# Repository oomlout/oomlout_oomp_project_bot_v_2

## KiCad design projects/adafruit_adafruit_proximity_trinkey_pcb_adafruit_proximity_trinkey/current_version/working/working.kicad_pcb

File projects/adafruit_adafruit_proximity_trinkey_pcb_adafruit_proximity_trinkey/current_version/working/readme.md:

# adafruit_proximity_trinkey_pcb
 
## summary 
* id: adafruit_adafruit_proximity_trinkey_pcb_adafruit_proximity_trinkey
* user: adafruit
* name: adafruit_proximity_trinkey_pcb
* board: adafruit_proximity_trinkey
* repo: https://github.com/adafruit/Adafruit-Proximity-Trinkey-PCB

* src_file_repo_sch: 
* src_file_repo_sch_link: https://github.com/adafruit/Adafruit-Proximity-Trinkey-PCB/tree/main/
* full details link: https://github.com/oomlout/oomlout_oomp_project_bot_v_2/tree/main/projects/adafruit_adafruit_proximity_trinkey_pcb_adafruit_proximity_trinkey/current_version/working  

## schematic  
  
[schematic (pdf)](working_schematic.pdf) 

## pcb  

[board (pdf)](working.pdf)  

## working_bom
| Id | Designator | Footprint | Quantity | Designation | Supplier and ref |  | None | 
| --- | --- | --- | --- | --- | --- | --- | --- | 
| 1 | R1,R2 | 0603-NO | 2 | 4.7K |  |  | [''] | 
| 2 | FID1,FID2 | FIDUCIAL_1MM | 2 | FIDUCIAL_1MM |  |  | [''] | 
| 3 | C3,C8 | 0805-NO | 2 | 10uF |  |  | [''] | 
| 4 | C4,C5 | 0603-NO | 2 | 1uF |  |  | [''] | 
| 5 | IC3 | QFN32_5MM | 1 | ATSAMD21E |  |  | [''] | 
| 6 | LED1,LED2 | LED3535 | 2 | WS2812B3535 |  |  | [''] | 
| 7 | U3 | APDS-9960 | 1 | APDS-9960 |  |  | [''] | 
| 8 | U1 | SOT23-5 | 1 | AP2112K-3.3 |  |  | [''] | 
| 9 | CN1 | USBA_PCB | 1 | USB A |  |  | [''] | 
| 10 | Q2 | BTN_KMR2_4.6X2.8 | 1 | reset |  |  | [''] | 
| 11 | SWD0,RST0 | TP16R | 2 | TPTP16R |  |  | [''] | 
| 12 | TP1,TP2 | TESTPOINT_ROUND_1.5MM_NO | 2 |  |  |  | [''] | 
| 13 | SWC0 | TP15R | 1 | TPTP15R |  |  | [''] | 
| 14 | U$8 | PCBFEAT-REV-040 | 1 |  |  |  | [''] | 
| 15 | U$10 | ADAFRUIT_9MM | 1 |  |  |  | [''] | 

## bom_schematic
| Ref | Qnty | Value | Cmp name | Footprint | Description | Vendor | DNP | 
| --- | --- | --- | --- | --- | --- | --- | --- | 
| C3, C8 | 2 | 10uF | CAP_CERAMIC0805-NOOUTLINE | working:0805-NO |  |  |  | 
| C4, C5 | 2 | 1uF | CAP_CERAMIC0603_NO | working:0603-NO |  |  |  | 
| CN1 | 1 | USB A | USB_TYPEAPCB | working:USBA_PCB |  |  |  | 
| FID1, FID2 | 2 | FIDUCIAL_1MM | FIDUCIAL_1MM | working:FIDUCIAL_1MM |  |  |  | 
| IC3 | 1 | ATSAMD21E | ATSAMD21E | working:QFN32_5MM |  |  |  | 
| LED1, LED2 | 2 | WS2812B3535 | WS2812B3535 | working:LED3535 |  |  |  | 
| Q2 | 1 | reset | SWITCH_TACT_SMT4.6X2.8 | working:BTN_KMR2_4.6X2.8 |  |  |  | 
| R1, R2 | 2 | 4.7K | RESISTOR_0603_NOOUT | working:0603-NO |  |  |  | 
| RST0 | 1 | TPTP16R | TPTP16R | working:TP16R |  |  |  | 
| SWC0 | 1 | TPTP15R | TPTP15R | working:TP15R |  |  |  | 
| SWD0 | 1 | TPTP16R | TPTP16R | working:TP16R |  |  |  | 
| TP1, TP2 | 2 | TESTPOINTROUND1.5MMNO | TESTPOINTROUND1.5MMNO | working:TESTPOINT_ROUND_1.5MM_NO |  |  |  | 
| U1 | 1 | AP2112K-3.3 | VREG_SOT23-5 | working:SOT23-5 |  |  |  | 
| U3 | 1 | APDS-9960 | APDS-9960 | working:APDS-9960 |  |  |  |

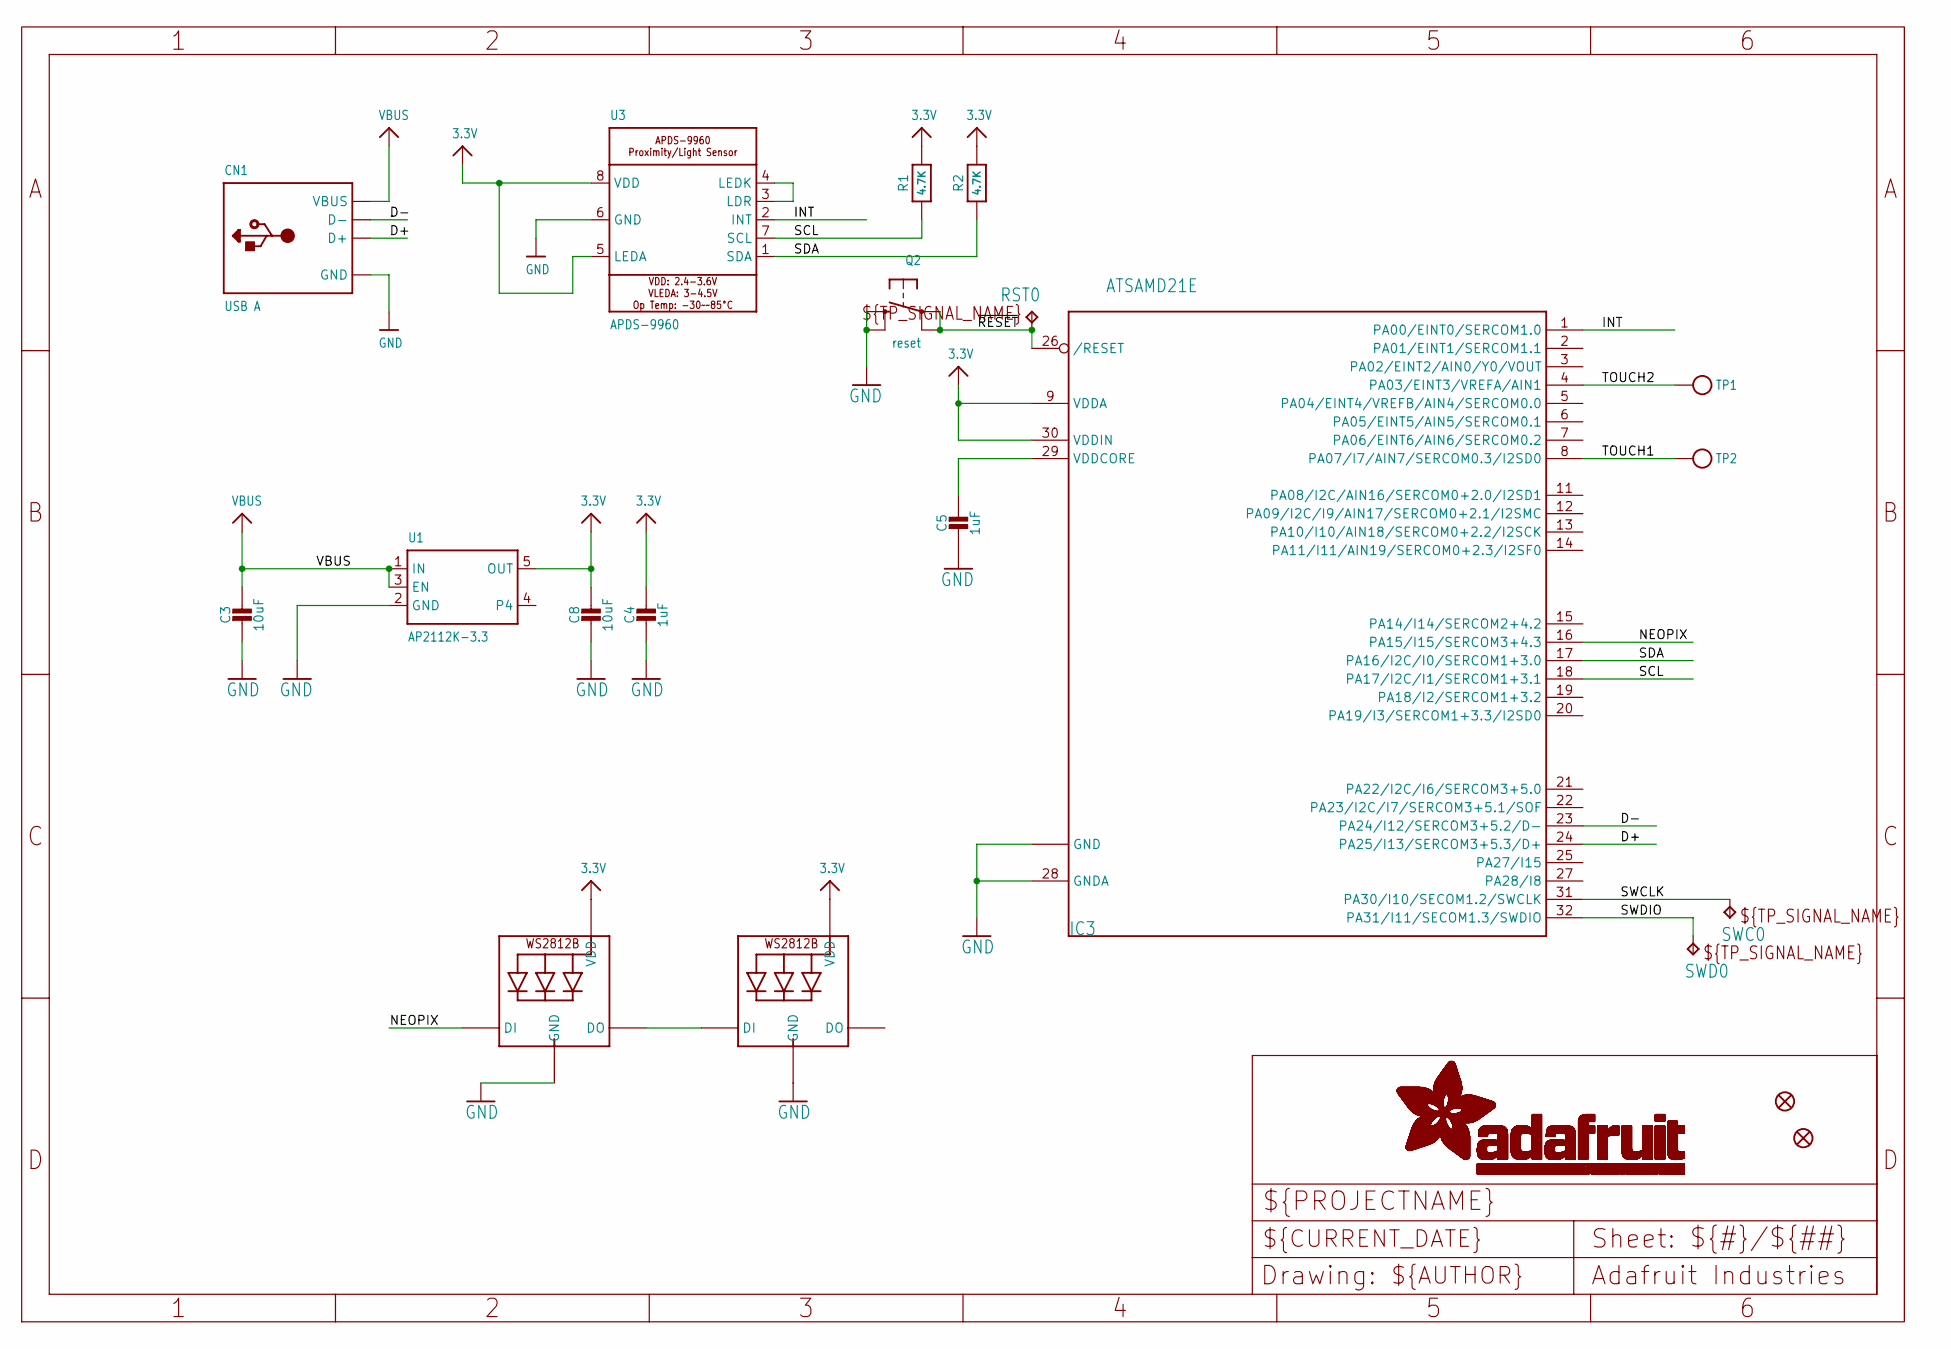
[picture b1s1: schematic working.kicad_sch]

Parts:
C3, C8: 10uF; 0805-NO
C4, C5: 1uF; 0603-NO
CN1: USB A; USBA_PCB
FID1, FID2: FIDUCIAL_1MM
IC3: ATSAMD21E; QFN32_5MM
LED1, LED2: WS2812B3535; LED3535
Q2: reset; BTN_KMR2_4.6X2.8
R1, R2: 4.7K; 0603-NO
RST0: TPTP16R; TP16R
SWC0: TPTP15R; TP15R
SWD0: TPTP16R; TP16R
TP1, TP2: TESTPOINTROUND1.5MMNO; TESTPOINT_ROUND_1.5MM_NO
U1: AP2112K-3.3; SOT23-5
U3: APDS-9960

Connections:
3.3V: C4.1, C8.1, IC3.9 (VDDA), IC3.30 (VDDIN), LED1.2 (VDD), LED2.2 (VDD), R1.2, R2.2, U1.5 (OUT), U3.5 (LEDA), U3.8 (VDD)
D+: CN1.USB_PLUS (D+), IC3.24 (PA25/I13/SERCOM3+5.3/D+)
D-: CN1.USB_NEG (D-), IC3.23 (PA24/I12/SERCOM3+5.2/D-)
GND: C3.2, C4.2, C5.2, C8.2, CN1.GND, IC3.10 (GND), IC3.28 (GNDA), IC3.33 (GND), LED1.4 (GND), LED2.4 (GND), Q2.B (S), Q2.B' (S1), U1.2 (GND), U3.6 (GND)
INT: IC3.1 (PA00/EINT0/SERCOM1.0), U3.2 (INT)
unnamed: LED1.1 (DI), LED2.3 (DO)
unnamed: U3.3 (LDR), U3.4 (LEDK)
NEOPIX: IC3.16 (PA15/I15/SERCOM3+4.3), LED2.1 (DI)
SCL: IC3.18 (PA17/I2C/I1/SERCOM1+3.1), R1.1, U3.7 (SCL)
SDA: IC3.17 (PA16/I2C/I0/SERCOM1+3.0), R2.1, U3.1 (SDA)
SWCLK: IC3.31 (PA30/I10/SECOM1.2/SWCLK), SWC0.TP
SWDIO: IC3.32 (PA31/I11/SECOM1.3/SWDIO), SWD0.TP
TOUCH1: IC3.8 (PA07/I7/AIN7/SERCOM0.3/I2SD0), TP2.P$1
TOUCH2: IC3.4 (PA03/EINT3/VREFA/AIN1), TP1.P$1
VBUS: C3.1, CN1.VCC (VBUS), U1.1 (IN), U1.3 (EN)
VDDCORE1: C5.1, IC3.29 (VDDCORE)
~RESET: IC3.26 (/RESET), Q2.A, Q2.A' (P1), RST0.TP

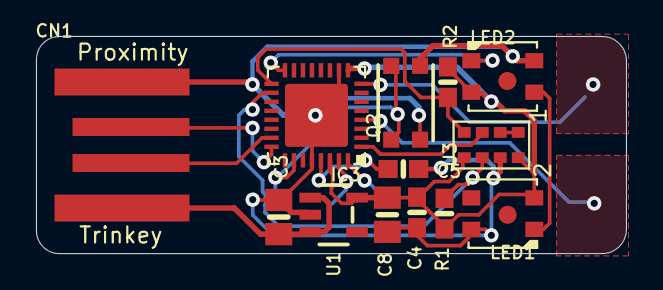
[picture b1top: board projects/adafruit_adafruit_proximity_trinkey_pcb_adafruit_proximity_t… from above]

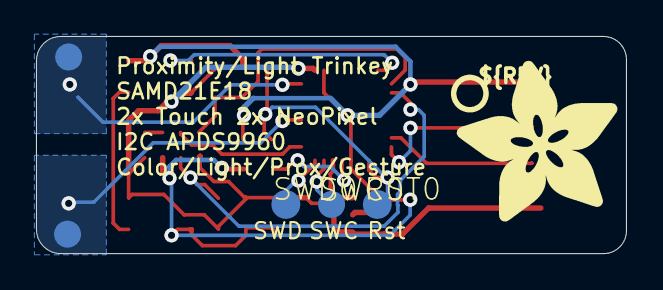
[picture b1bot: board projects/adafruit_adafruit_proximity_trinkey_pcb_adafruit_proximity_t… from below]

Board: 2 copper layers, 32.8 x 12.1 mm, 22 parts (7 on the bottom side), 17 nets.

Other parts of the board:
U$8: PCBFEAT-REV-040
U$10: ADAFRUIT_9MM

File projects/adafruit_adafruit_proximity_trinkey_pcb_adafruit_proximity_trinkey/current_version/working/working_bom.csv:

"Id";"Designator";"Footprint";"Quantity";"Designation";"Supplier and ref";
1;"R1,R2";"0603-NO";2;"4.7K";;;
2;"FID1,FID2";"FIDUCIAL_1MM";2;"FIDUCIAL_1MM";;;
3;"C3,C8";"0805-NO";2;"10uF";;;
4;"C4,C5";"0603-NO";2;"1uF";;;
5;"IC3";"QFN32_5MM";1;"ATSAMD21E";;;
6;"LED1,LED2";"LED3535";2;"WS2812B3535";;;
7;"U3";"APDS-9960";1;"APDS-9960";;;
8;"U1";"SOT23-5";1;"AP2112K-3.3";;;
9;"CN1";"USBA_PCB";1;"USB A";;;
10;"Q2";"BTN_KMR2_4.6X2.8";1;"reset";;;
11;"SWD0,RST0";"TP16R";2;"TPTP16R";;;
12;"TP1,TP2";"TESTPOINT_ROUND_1.5MM_NO";2;"";;;
13;"SWC0";"TP15R";1;"TPTP15R";;;
14;"U$8";"PCBFEAT-REV-040";1;"";;;
15;"U$10";"ADAFRUIT_9MM";1;"";;;

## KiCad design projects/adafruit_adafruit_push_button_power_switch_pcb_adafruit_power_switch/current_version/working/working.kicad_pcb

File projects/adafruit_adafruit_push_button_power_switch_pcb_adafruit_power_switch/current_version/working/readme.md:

# adafruit_push_button_power_switch_pcb
 
## summary 
* id: adafruit_adafruit_push_button_power_switch_pcb_adafruit_power_switch
* user: adafruit
* name: adafruit_push_button_power_switch_pcb
* board: adafruit_power_switch
* repo: https://github.com/adafruit/Adafruit-Push-Button-Power-Switch-PCB

* src_file_repo_sch: 
* src_file_repo_sch_link: https://github.com/adafruit/Adafruit-Push-Button-Power-Switch-PCB/tree/master/
* full details link: https://github.com/oomlout/oomlout_oomp_project_bot_v_2/tree/main/projects/adafruit_adafruit_push_button_power_switch_pcb_adafruit_power_switch/current_version/working  

## schematic  
  
[schematic (pdf)](working_schematic.pdf) 

## pcb  

[board (pdf)](working.pdf)  

## working_bom
| Id | Designator | Footprint | Quantity | Designation | Supplier and ref |  | None | 
| --- | --- | --- | --- | --- | --- | --- | --- | 
| 1 | FID1,FID3,FID2 | FIDUCIAL_1MM | 3 | FIDUCIAL" |  |  | [''] | 
| 2 | @HOLE2,@HOLE3,@HOLE0,@HOLE1 |  | 4 |  |  |  | [''] | 
| 3 | R4,R1 | R0805 | 2 | 1K |  |  | [''] | 
| 4 | R2,R3 | R0805 | 2 | 100K |  |  | [''] | 
| 5 | Q2 | SOT23-WIDE | 1 | POWER PFET |  |  | [''] | 
| 6 | U$2,U$1 | ADAFRUIT_2.5MM | 2 |  |  |  | [''] | 
| 7 | C1 | C0805 | 1 | 0.1uF |  |  | [''] | 
| 8 | IC1 | MC14093B-TSSOP14 | 1 | 4093DT |  |  | [''] | 
| 9 | LED0 | CHIP-LED0805 | 1 | RED |  |  | [''] | 
| 10 | Q1 | SOT23-BEC | 1 | 2N2222 |  |  | [''] | 
| 11 | CN2,CN1 | 1X04-CLEANBIG | 2 | 1X4-CLEANBIG |  |  | [''] | 
| 12 | S1 | B3F-40XX-ROUND | 1 |  |  |  | [''] | 

## bom_schematic
| Ref | Qnty | Value | Cmp name | Footprint | Description | Vendor | DNP | 
| --- | --- | --- | --- | --- | --- | --- | --- | 
| C1 | 1 | 0.1uF | C-USC0805 | working:C0805 |  |  |  | 
| CN1, CN2 | 2 | 1X4-CLEANBIG | 1X4-CLEANBIG | working:1X04-CLEANBIG |  |  |  | 
| FID1, FID2, FID3 | 3 | FIDUCIAL"" | FIDUCIAL{dblquote}{dblquote} | working:FIDUCIAL_1MM |  |  |  | 
| IC1 | 1 | 4093DT | 4093DT | working:MC14093B-TSSOP14 |  |  |  | 
| LED0 | 1 | RED | LEDCHIP-LED0805 | working:CHIP-LED0805 |  |  |  | 
| Q1 | 1 | 2N2222 | -NPN-SOT23-BEC | working:SOT23-BEC |  |  |  | 
| Q2 | 1 | POWER PFET | MOSFET-PWIDE | working:SOT23-WIDE |  |  |  | 
| R1, R4 | 2 | 1K | R-US_R0805 | working:R0805 |  |  |  | 
| R2, R3 | 2 | 100K | rcl_R-US_R0805 | working:R0805 |  |  |  | 
| S1 | 1 | 40-XX-ROUND | 40-XX-ROUND | working:B3F-40XX-ROUND |  |  |  |

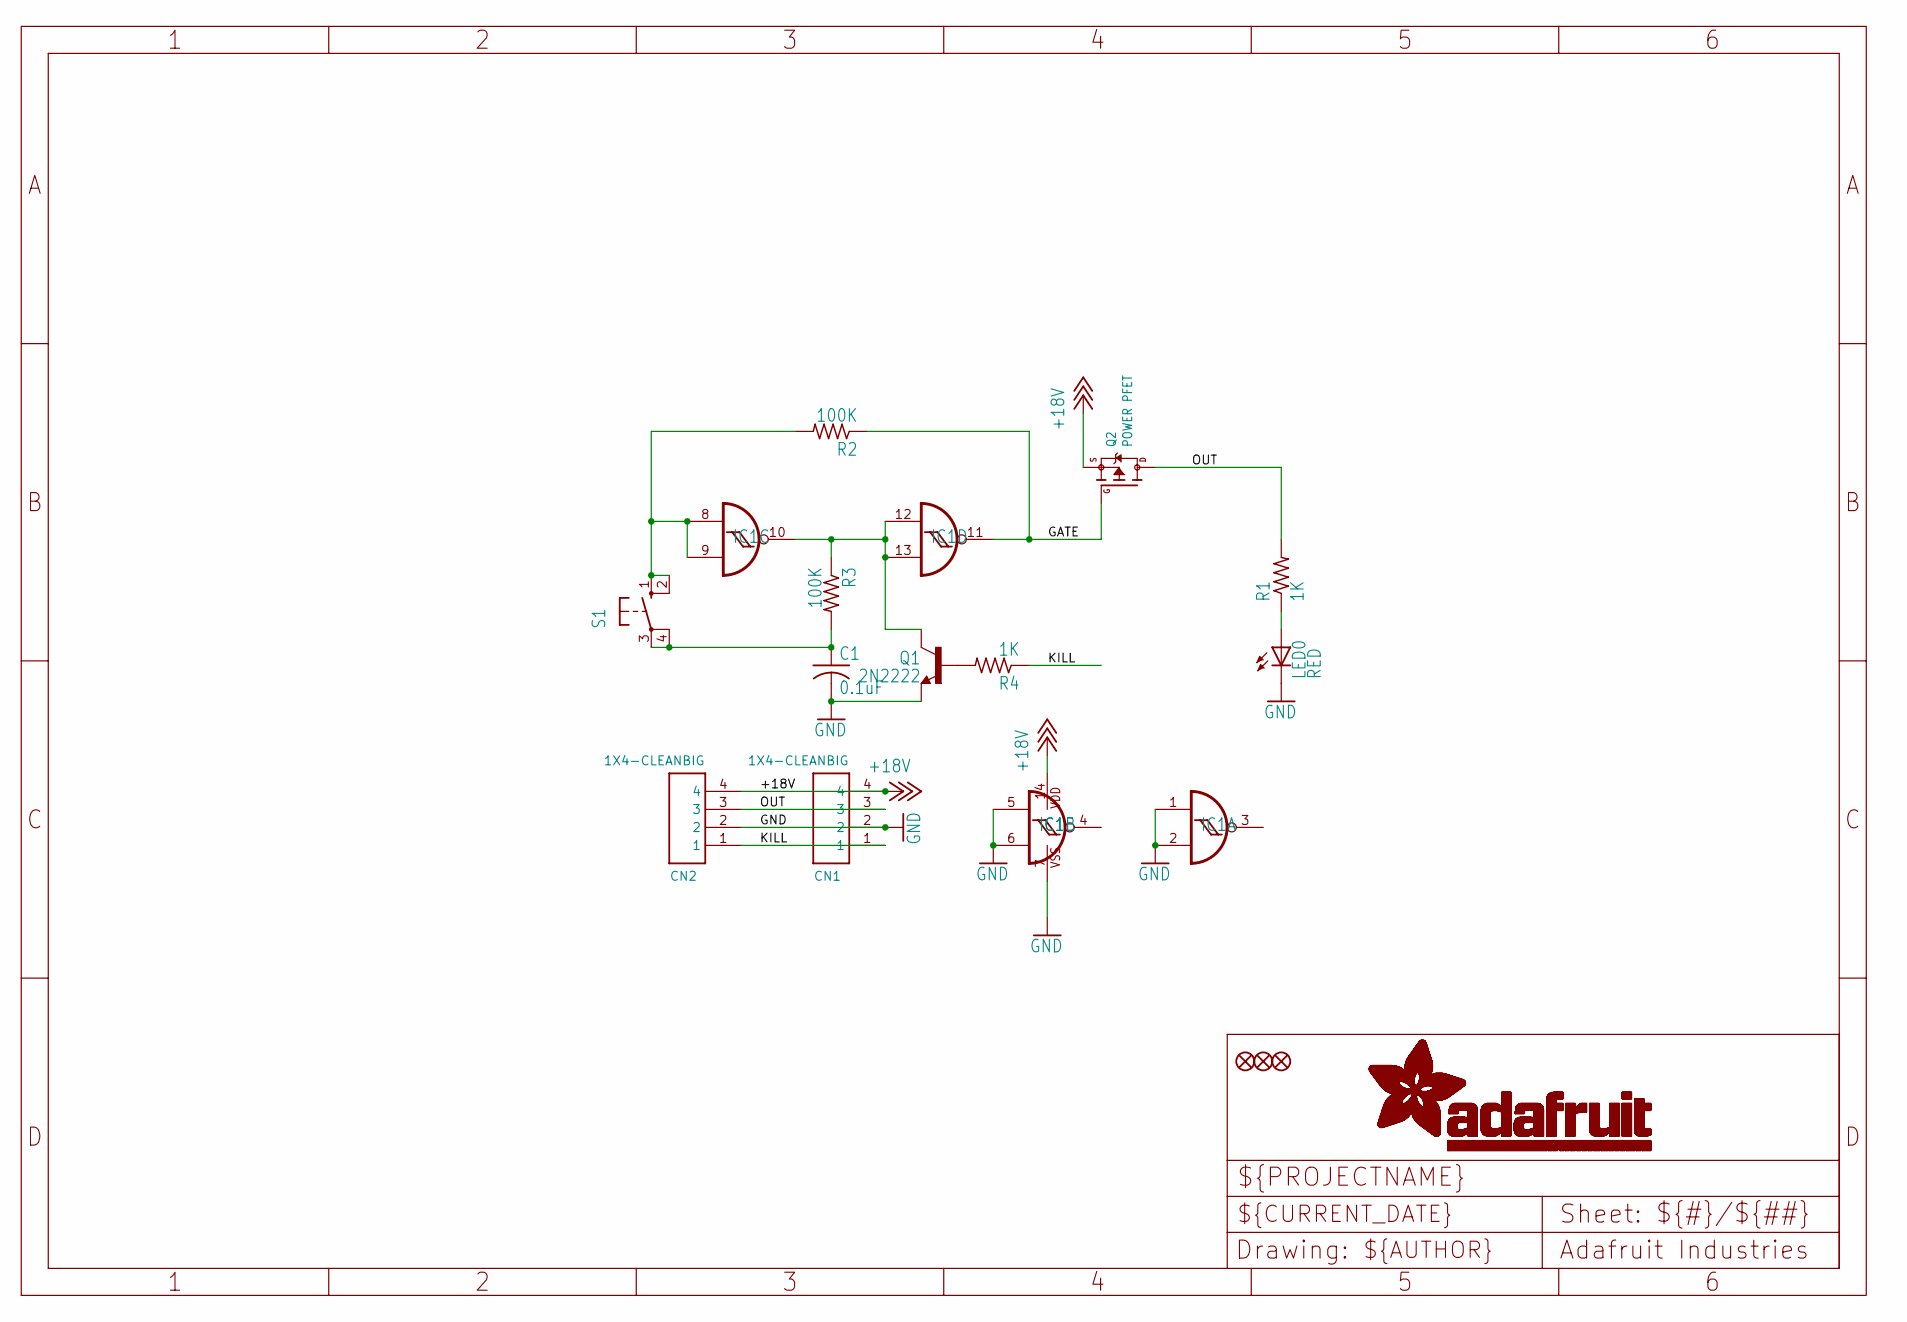
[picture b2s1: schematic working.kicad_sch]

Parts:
C1: 0.1uF; C0805
CN1, CN2: 1X4-CLEANBIG; 1X04-CLEANBIG
FID1, FID2, FID3: FIDUCIAL""; FIDUCIAL_1MM
IC1: 4093DT; MC14093B-TSSOP14
LED0: RED; CHIP-LED0805
Q1: 2N2222; SOT23-BEC
Q2: POWER PFET; SOT23-WIDE
R1, R4: 1K; R0805
R2, R3: 100K; R0805
S1: 40-XX-ROUND; B3F-40XX-ROUND

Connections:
+18V: CN1.4, CN2.4, IC1.14 (VDD), Q2.2 (S)
GATE: IC1.11 (O), Q2.1 (G), R2.1
GND: C1.2, CN1.2, CN2.2, IC1.1 (I0), IC1.2 (I1), IC1.5 (I0), IC1.6 (I1), IC1.7 (VSS), LED0.C, Q1.E
KILL: CN1.1, CN2.1, R4.1
unnamed: Q1.B, R4.2
unnamed: IC1.10 (O), IC1.12 (I0), IC1.13 (I1), Q1.C, R3.1
unnamed: LED0.A, R1.1
unnamed: C1.1, R3.2, S1.3, S1.4 (P1)
unnamed: IC1.8 (I0), IC1.9 (I1), R2.2, S1.1 (S), S1.2 (S1)
OUT: CN1.3, CN2.3, Q2.3 (D), R1.2

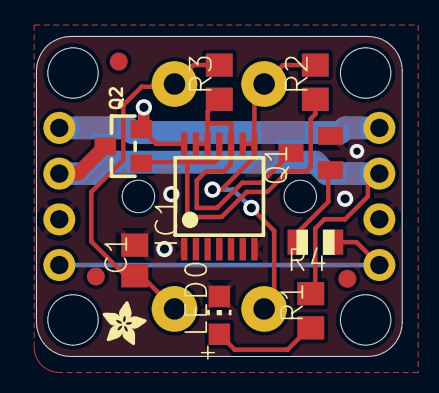
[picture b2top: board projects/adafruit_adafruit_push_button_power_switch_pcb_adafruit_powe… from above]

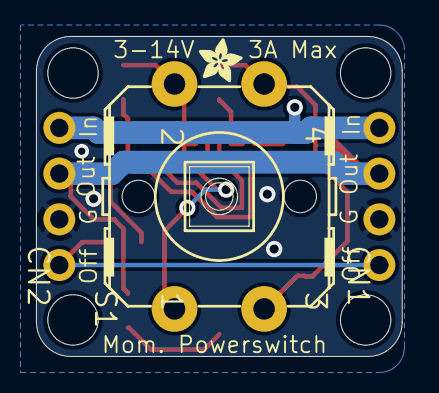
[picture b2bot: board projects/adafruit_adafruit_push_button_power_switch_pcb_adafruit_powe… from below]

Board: 2 copper layers, 20.3 x 17.8 mm, 21 parts (4 on the bottom side), 10 nets.

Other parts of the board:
@HOLE0, @HOLE1, @HOLE2, @HOLE3: (no value)
U$1, U$2: ADAFRUIT_2.5MM

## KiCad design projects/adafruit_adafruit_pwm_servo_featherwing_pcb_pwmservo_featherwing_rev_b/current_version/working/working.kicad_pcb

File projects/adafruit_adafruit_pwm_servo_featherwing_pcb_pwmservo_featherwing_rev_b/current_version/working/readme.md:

# adafruit_pwm_servo_featherwing_pcb
 
## summary 
* id: adafruit_adafruit_pwm_servo_featherwing_pcb_pwmservo_featherwing_rev_b
* user: adafruit
* name: adafruit_pwm_servo_featherwing_pcb
* board: pwmservo_featherwing_rev_b
* repo: https://github.com/adafruit/Adafruit-PWM-Servo-FeatherWing-PCB

* src_file_repo_sch: 
* src_file_repo_sch_link: https://github.com/adafruit/Adafruit-PWM-Servo-FeatherWing-PCB/tree/master/
* full details link: https://github.com/oomlout/oomlout_oomp_project_bot_v_2/tree/main/projects/adafruit_adafruit_pwm_servo_featherwing_pcb_pwmservo_featherwing_rev_b/current_version/working  

## schematic  
  
[schematic (pdf)](working_schematic.pdf) 

## pcb  

[board (pdf)](working.pdf)  

## working_bom
| Id | Designator | Footprint | Quantity | Designation | Supplier and ref |  | None | 
| --- | --- | --- | --- | --- | --- | --- | --- | 
| 1 | LED1 | CHIPLED_0805_NOOUTLINE | 1 | GREEN |  |  | [''] | 
| 2 | JP3 | 1X16_ROUND | 1 |  |  |  | [''] | 
| 3 | R11,R13 | RESPACK_4X0603 | 2 | 220 |  |  | [''] | 
| 4 | R7 | 0805-NO | 1 | 10K |  |  | [''] | 
| 5 | Q1 | POWERDI3333 | 1 | AON7401 |  |  | [''] | 
| 6 | J1 | TERMBLOCK_1X2-3.5MM | 1 |  |  |  | [''] | 
| 7 | C1 | 0805-NO | 1 | 10uF |  |  | [''] | 
| 8 | JP4 | 1X12_ROUND | 1 |  |  |  | [''] | 
| 9 | R2,R1 | RESPACK_4X0603 | 2 | 10K |  |  | [''] | 
| 10 | JP1,JP2 | 3X04 | 2 |  |  |  | [''] | 
| 11 | FID2,FID1 | FIDUCIAL_1MM | 2 | FIDUCIAL" |  |  | [''] | 
| 12 | MS1 | FEATHERWING | 1 | FEATHERWING |  |  | [''] | 
| 13 | SW1 | BTN_KMR2_4.6X2.8 | 1 |  |  |  | [''] | 
| 14 | C2 | E3,5-8 | 1 |  |  |  | [''] | 
| 15 | U$14 | ADAFRUIT_3.5MM | 1 |  |  |  | [''] | 
| 16 | R10 | 0805-NO | 1 | 470 |  |  | [''] | 
| 17 | U1 | TSSOP28 | 1 | PCA9685 |  |  | [''] | 
| 18 | U$12 | SYMBOL_MINUS | 1 |  |  |  | [''] | 
| 19 | U$11 | SYMBOL_PLUS | 1 |  |  |  | [''] | 
| 20 | SJ_A4,SJ_A3,SJ_A5,SJ_A1,SJ_A0,SJ_A2 | SOLDERJUMPER_REFLOW_NOPASTE | 6 |  |  |  | [''] | 
| 21 | U$16 | PCBFEAT-REV-040 | 1 |  |  |  | [''] | 
| 22 | U$15 | FEATHERLOGO | 1 |  |  |  | [''] | 

## bom_schematic
| Ref | Qnty | Value | Cmp name | Footprint | Description | Vendor | DNP | 
| --- | --- | --- | --- | --- | --- | --- | --- | 
| C1 | 1 | 10uF | CAP_CERAMIC0805-NOOUTLINE | working:0805-NO |  |  |  | 
| C2 | 1 | CPOL-USE3.5-8 | CPOL-USE3.5-8 | working:E3,5-8 |  |  |  | 
| FID1, FID2 | 2 | FIDUCIAL"" | FIDUCIAL{dblquote}{dblquote} | working:FIDUCIAL_1MM |  |  |  | 
| J1 | 1 | TERMBLOCK_1X2 | TERMBLOCK_1X2 | working:TERMBLOCK_1X2-3.5MM |  |  |  | 
| JP1, JP2 | 2 | HEADER-3X04 | HEADER-3X04 | working:3X04 |  |  |  | 
| JP3 | 1 | HEADER-1X16ROUND | HEADER-1X16ROUND | working:1X16_ROUND |  |  |  | 
| JP4 | 1 | HEADER-1X12 | HEADER-1X12 | working:1X12_ROUND |  |  |  | 
| LED1 | 1 | GREEN | LED0805_NOOUTLINE | working:CHIPLED_0805_NOOUTLINE |  |  |  | 
| MS1 | 1 | FEATHERWING | FEATHERWING | working:FEATHERWING |  |  |  | 
| Q1 | 1 | AON7401 | MOSFET-P-POWERDI3333 | working:POWERDI3333 |  |  |  | 
| R1, R2 | 2 | 10K | RESISTOR_4PACK | working:RESPACK_4X0603 |  |  |  | 
| R7 | 1 | 10K | RESISTOR0805_NOOUTLINE | working:0805-NO |  |  |  | 
| R10 | 1 | 470 | RESISTOR0805_NOOUTLINE | working:0805-NO |  |  |  | 
| R11, R13 | 2 | 220 | RESISTOR_4PACK | working:RESPACK_4X0603 |  |  |  | 
| SJ_A0, SJ_A1, SJ_A2, SJ_A3, SJ_A4, SJ_A5 | 6 | SOLDERJUMPERREFLOW_NOPASTE | SOLDERJUMPERREFLOW_NOPASTE | working:SOLDERJUMPER_REFLOW_NOPASTE |  |  |  | 
| SW1 | 1 | SWITCH_TACT_SMT4.6X2.8 | SWITCH_TACT_SMT4.6X2.8 | working:BTN_KMR2_4.6X2.8 |  |  |  | 
| U1 | 1 | PCA9685 | PCA9685 | working:TSSOP28 |  |  |  |

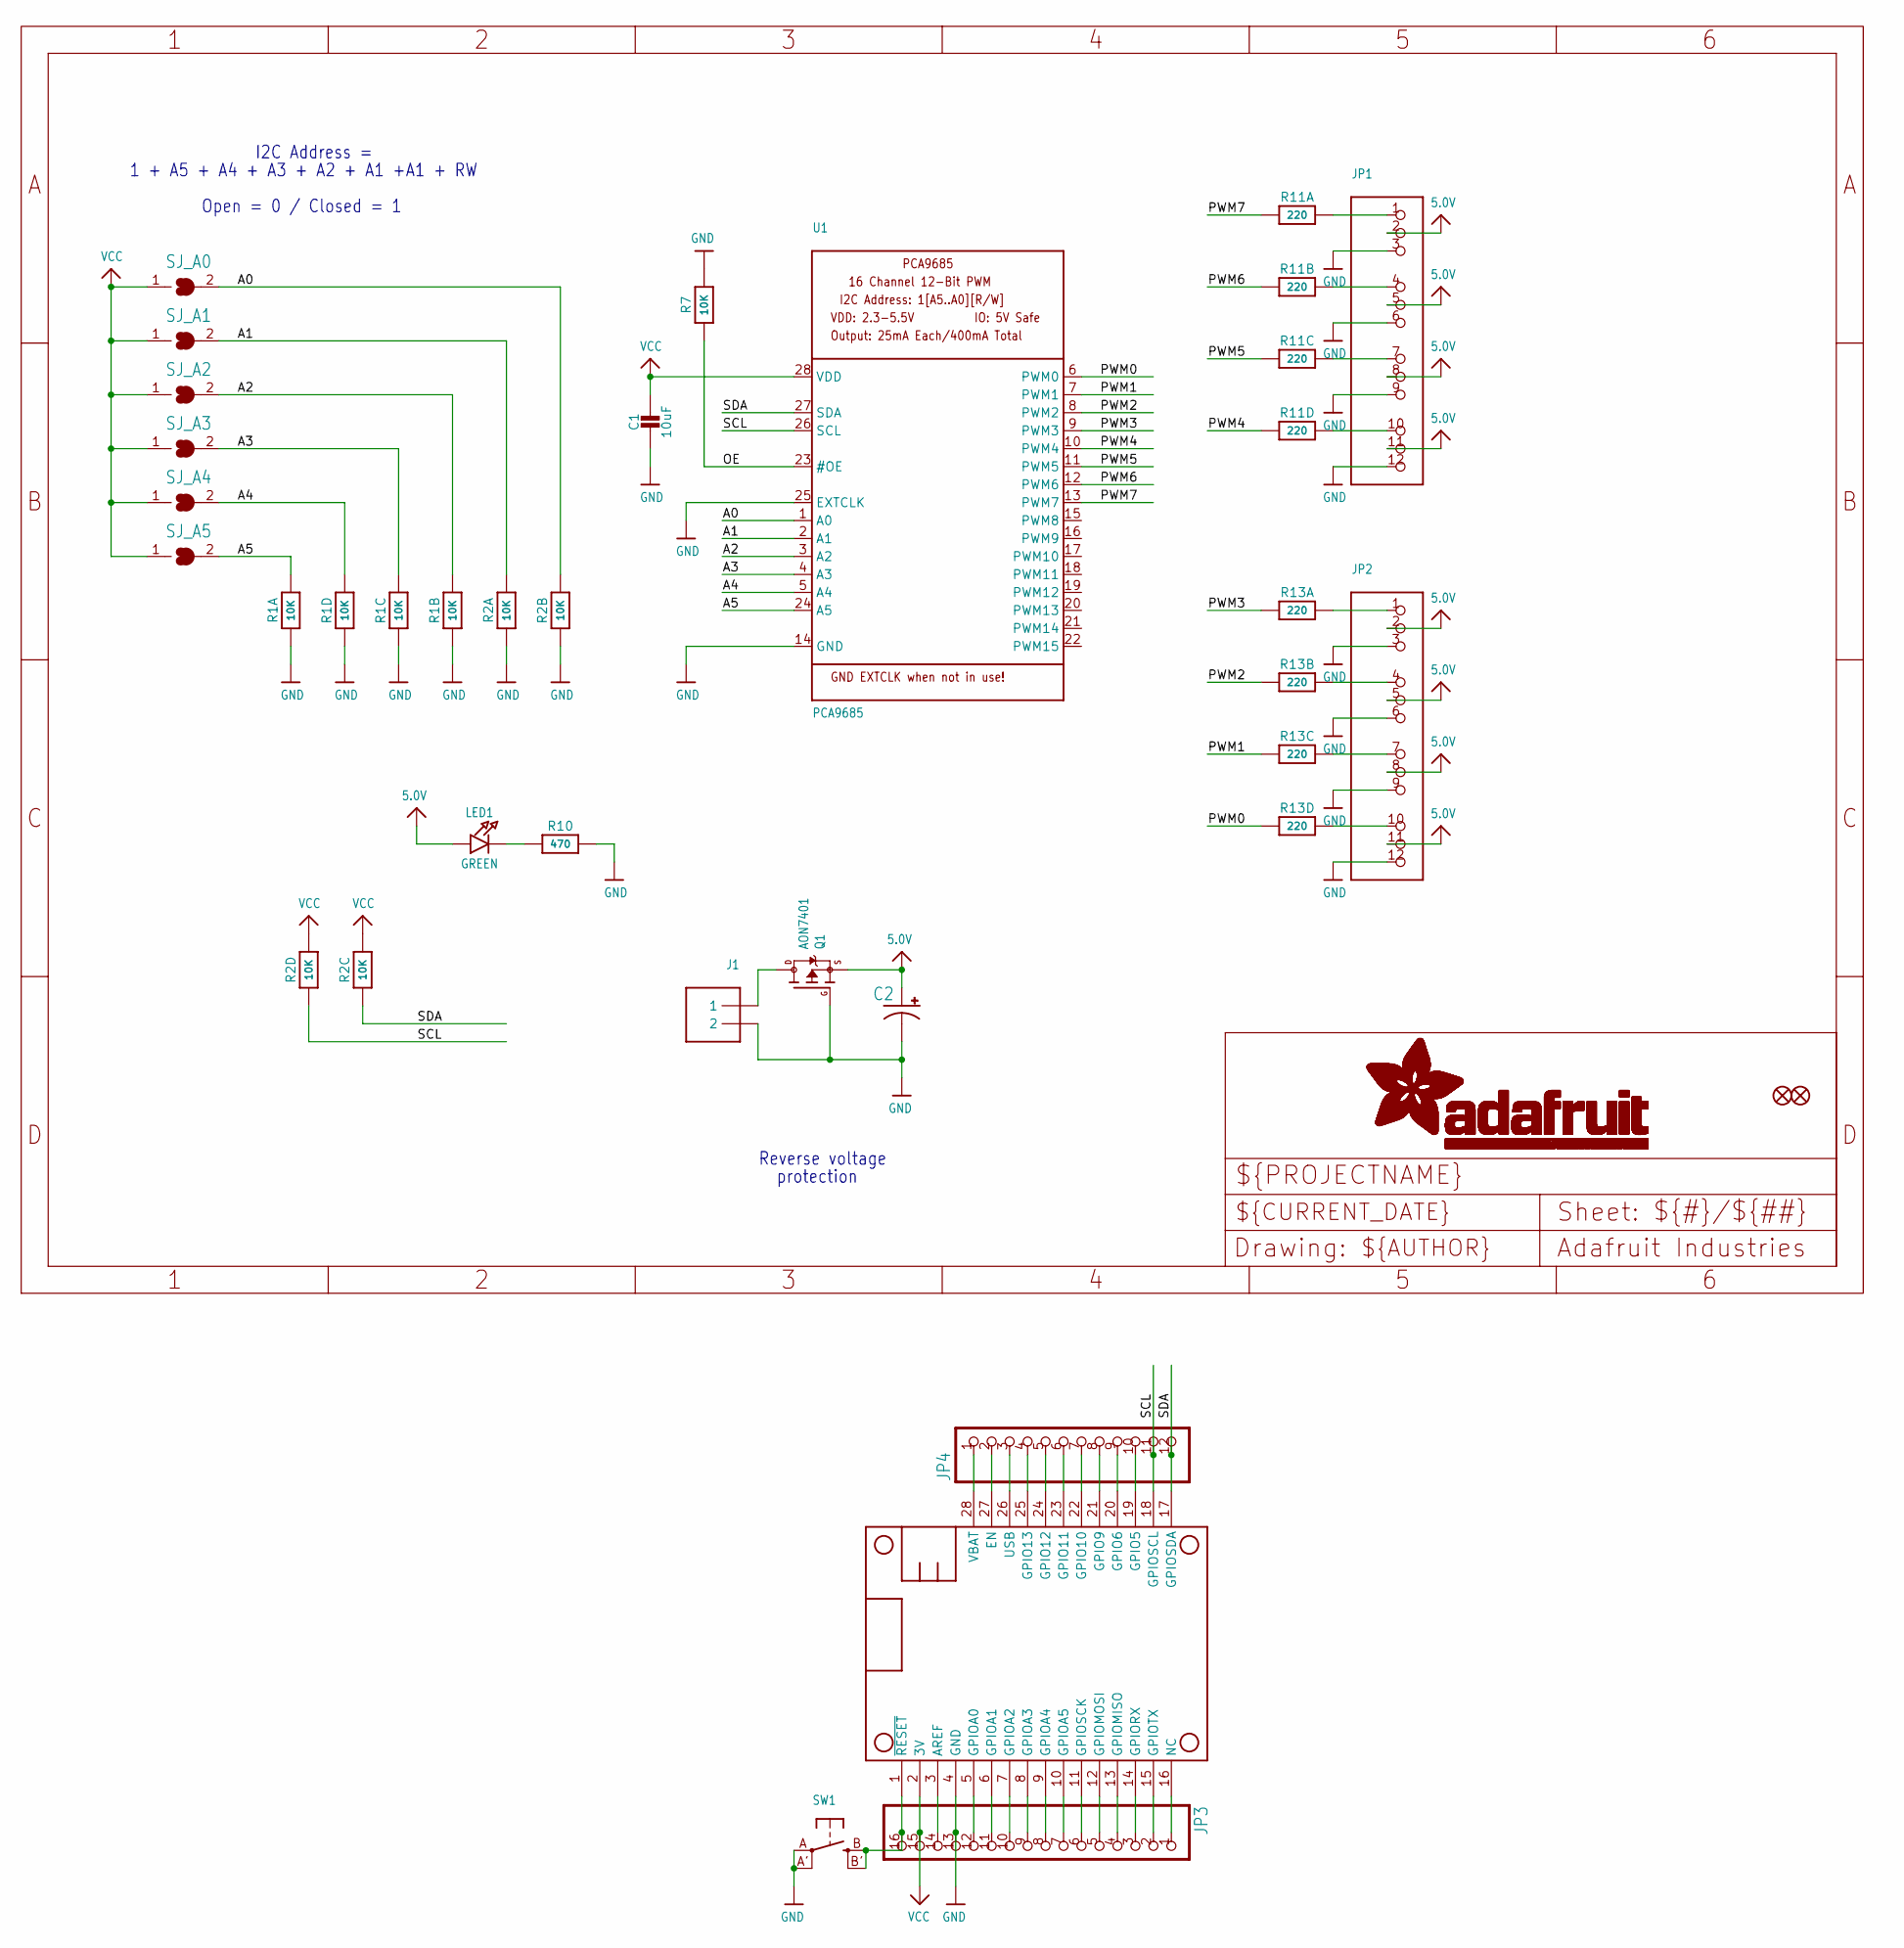
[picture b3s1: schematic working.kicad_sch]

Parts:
C1: 10uF; 0805-NO
C2: CPOL-USE3.5-8; E3,5-8
FID1, FID2: FIDUCIAL""; FIDUCIAL_1MM
J1: TERMBLOCK_1X2; TERMBLOCK_1X2-3.5MM
JP1, JP2: HEADER-3X04; 3X04
JP3: HEADER-1X16ROUND; 1X16_ROUND
JP4: HEADER-1X12; 1X12_ROUND
LED1: GREEN; CHIPLED_0805_NOOUTLINE
MS1: FEATHERWING
Q1: AON7401; POWERDI3333
R1, R2: 10K; RESPACK_4X0603
R7: 10K; 0805-NO
R10: 470; 0805-NO
R11, R13: 220; RESPACK_4X0603
SJ_A0, SJ_A1, SJ_A2, SJ_A3, SJ_A4, SJ_A5: SOLDERJUMPERREFLOW_NOPASTE; SOLDERJUMPER_REFLOW_NOPASTE
SW1: SWITCH_TACT_SMT4.6X2.8; BTN_KMR2_4.6X2.8
U1: PCA9685; TSSOP28

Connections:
5.0V: C2.+, JP1.2, JP1.5, JP1.8, JP1.11, JP2.2, JP2.5, JP2.8, JP2.11, LED1.A, Q1.1 (S), Q1.2 (S), Q1.3 (S)
A0: R2.7 (2), SJ_A0.2, U1.1 (A0)
A1: R2.8 (2), SJ_A1.2, U1.2 (A1)
A2: R1.7 (2), SJ_A2.2, U1.3 (A2)
A3: R1.6 (2), SJ_A3.2, U1.4 (A3)
A4: R1.5 (2), SJ_A4.2, U1.5 (A4)
A5: R1.8 (2), SJ_A5.2, U1.24 (A5)
GND: C1.2, C2.-, J1.2, JP1.3, JP1.6, JP1.9, JP1.12, JP2.3, JP2.6, JP2.9, JP2.12, JP3.13, MS1.4 (GND), Q1.4 (G), R1.1, R1.2 (1), R1.3 (1), R1.4 (1), R2.1, R2.2 (1), R7.2, R10.2, SW1.A, SW1.A' (P1), U1.14 (GND), U1.25 (EXTCLK)
unnamed: LED1.C, R10.1
unnamed: JP1.4, R11.7 (2)
unnamed: JP1.1, R11.8 (2)
unnamed: JP1.7, R11.6 (2)
unnamed: JP1.10, R11.5 (2)
unnamed: JP2.1, R13.8 (2)
unnamed: JP2.4, R13.7 (2)
unnamed: JP2.7, R13.6 (2)
unnamed: JP2.10, R13.5 (2)
unnamed: JP3.1, MS1.16 (NC)
unnamed: JP3.2, MS1.15 (GPIOTX)
unnamed: JP3.3, MS1.14 (GPIORX)
unnamed: JP3.4, MS1.13 (GPIOMISO)
unnamed: JP3.5, MS1.12 (GPIOMOSI)
unnamed: JP3.6, MS1.11 (GPIOSCK)
unnamed: JP3.7, MS1.10 (GPIOA5)
unnamed: JP3.8, MS1.9 (GPIOA4)
unnamed: JP3.9, MS1.8 (GPIOA3)
unnamed: JP3.10, MS1.7 (GPIOA2)
unnamed: JP3.11, MS1.6 (GPIOA1)
unnamed: JP3.12, MS1.5 (GPIOA0)
unnamed: JP3.14, MS1.3 (AREF)
unnamed: JP4.2, MS1.27 (EN)
unnamed: JP4.4, MS1.25 (GPIO13)
unnamed: JP4.5, MS1.24 (GPIO12)
unnamed: JP4.6, MS1.23 (GPIO11)
unnamed: JP4.7, MS1.22 (GPIO10)
unnamed: JP4.8, MS1.21 (GPIO9)
unnamed: JP4.9, MS1.20 (GPIO6)
unnamed: JP4.10, MS1.19 (GPIO5)
unnamed: JP3.16, MS1.1 (~RESET), SW1.B (S), SW1.B' (S1)
OE: R7.1, U1.23 (#OE)
PWM0: R13.4 (1), U1.6 (PWM0)
PWM1: R13.3 (1), U1.7 (PWM1)
PWM2: R13.2 (1), U1.8 (PWM2)
PWM3: R13.1, U1.9 (PWM3)
PWM4: R11.4 (1), U1.10 (PWM4)
PWM5: R11.3 (1), U1.11 (PWM5)
PWM6: R11.2 (1), U1.12 (PWM6)
PWM7: R11.1, U1.13 (PWM7)
PWRIN: J1.1, Q1.5678 (D)
SCL: JP4.11, MS1.18 (GPIOSCL), R2.4 (1), U1.26 (SCL)
SDA: JP4.12, MS1.17 (GPIOSDA), R2.3 (1), U1.27 (SDA)
USB: JP4.3, MS1.26 (USB)
VBAT: JP4.1, MS1.28 (VBAT)
VCC: C1.1, JP3.15, MS1.2 (3V), R2.5 (2), R2.6 (2), SJ_A0.1, SJ_A1.1, SJ_A2.1, SJ_A3.1, SJ_A4.1, SJ_A5.1, U1.28 (VDD)

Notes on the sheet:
I2C Address =
Reverse voltage
Open = 0 / Closed = 1
protection
1 + A5 + A4 + A3 + A2 + A1 +A1 + RW

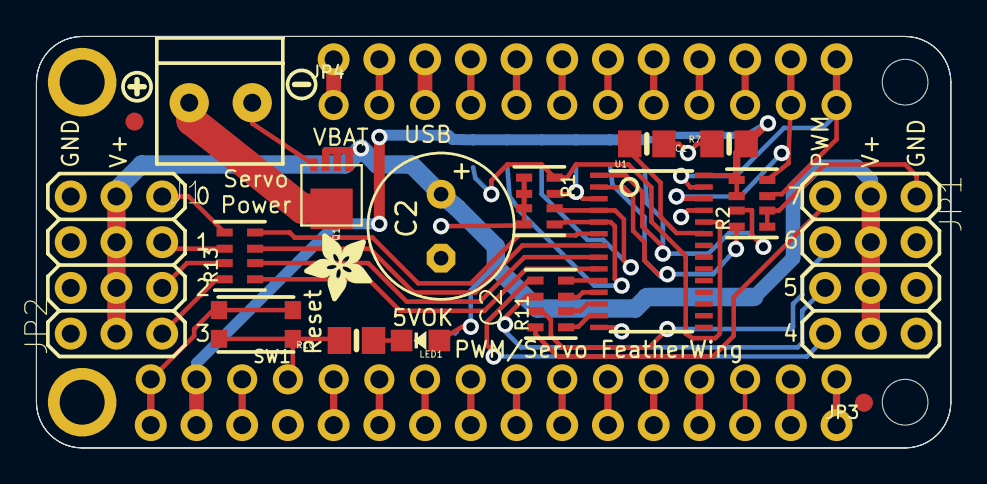
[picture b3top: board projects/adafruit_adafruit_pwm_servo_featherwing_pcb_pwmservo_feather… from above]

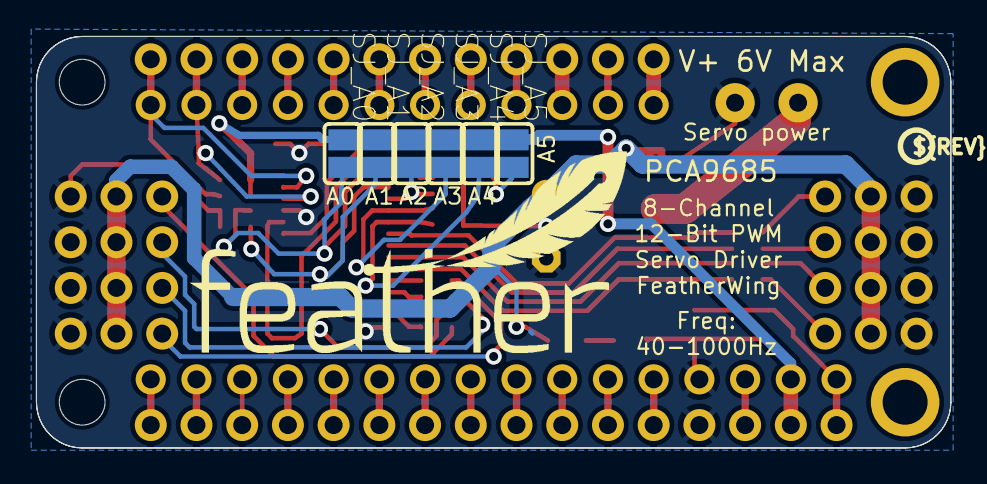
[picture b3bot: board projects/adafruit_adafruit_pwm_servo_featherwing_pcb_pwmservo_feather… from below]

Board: 2 copper layers, 50.8 x 22.9 mm, 31 parts (8 on the bottom side), 54 nets.

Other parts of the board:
U$11: SYMBOL_PLUS
U$12: SYMBOL_MINUS
U$14: ADAFRUIT_3.5MM
U$15: FEATHERLOGO
U$16: PCBFEAT-REV-040

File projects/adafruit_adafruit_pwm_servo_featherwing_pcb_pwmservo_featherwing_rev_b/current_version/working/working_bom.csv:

"Id";"Designator";"Footprint";"Quantity";"Designation";"Supplier and ref";
1;"LED1";"CHIPLED_0805_NOOUTLINE";1;"GREEN";;;
2;"JP3";"1X16_ROUND";1;"";;;
3;"R11,R13";"RESPACK_4X0603";2;"220";;;
4;"R7";"0805-NO";1;"10K";;;
5;"Q1";"POWERDI3333";1;"AON7401";;;
6;"J1";"TERMBLOCK_1X2-3.5MM";1;"";;;
7;"C1";"0805-NO";1;"10uF";;;
8;"JP4";"1X12_ROUND";1;"";;;
9;"R2,R1";"RESPACK_4X0603";2;"10K";;;
10;"JP1,JP2";"3X04";2;"";;;
11;"FID2,FID1";"FIDUCIAL_1MM";2;"FIDUCIAL""";;;
12;"MS1";"FEATHERWING";1;"FEATHERWING";;;
13;"SW1";"BTN_KMR2_4.6X2.8";1;"";;;
14;"C2";"E3,5-8";1;"";;;
15;"U$14";"ADAFRUIT_3.5MM";1;"";;;
16;"R10";"0805-NO";1;"470";;;
17;"U1";"TSSOP28";1;"PCA9685";;;
18;"U$12";"SYMBOL_MINUS";1;"";;;
19;"U$11";"SYMBOL_PLUS";1;"";;;
20;"SJ_A4,SJ_A3,SJ_A5,SJ_A1,SJ_A0,SJ_A2";"SOLDERJUMPER_REFLOW_NOPASTE";6;"";;;
21;"U$16";"PCBFEAT-REV-040";1;"";;;
22;"U$15";"FEATHERLOGO";1;"";;;
